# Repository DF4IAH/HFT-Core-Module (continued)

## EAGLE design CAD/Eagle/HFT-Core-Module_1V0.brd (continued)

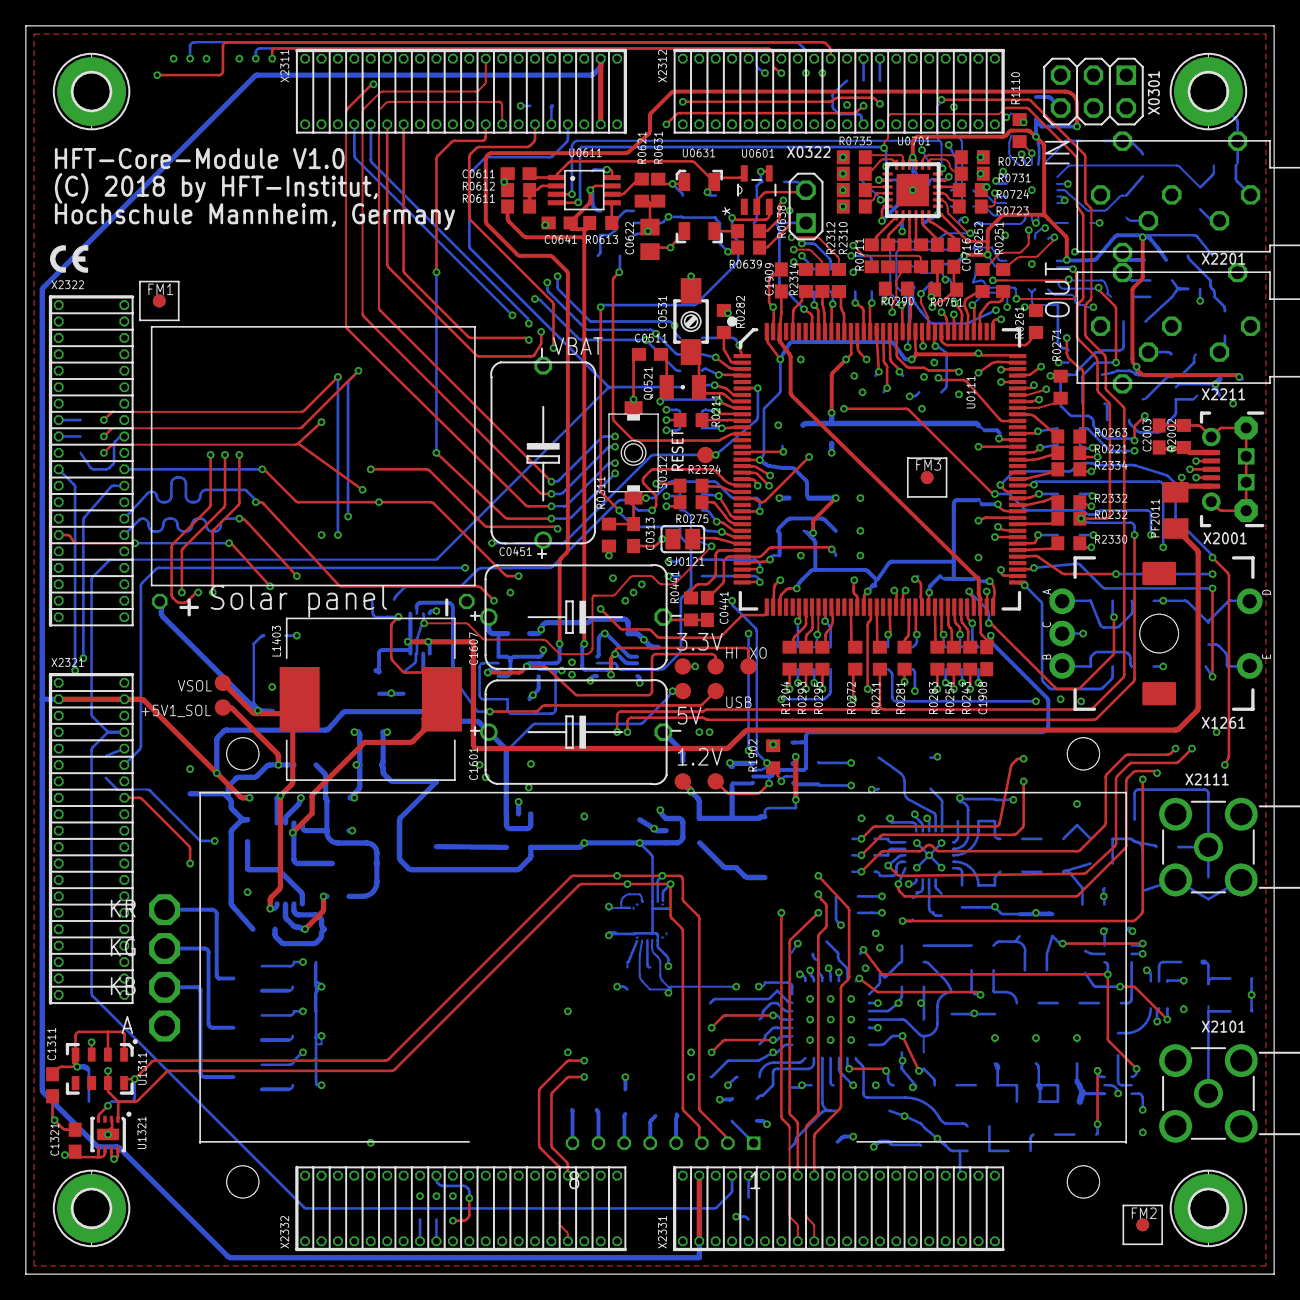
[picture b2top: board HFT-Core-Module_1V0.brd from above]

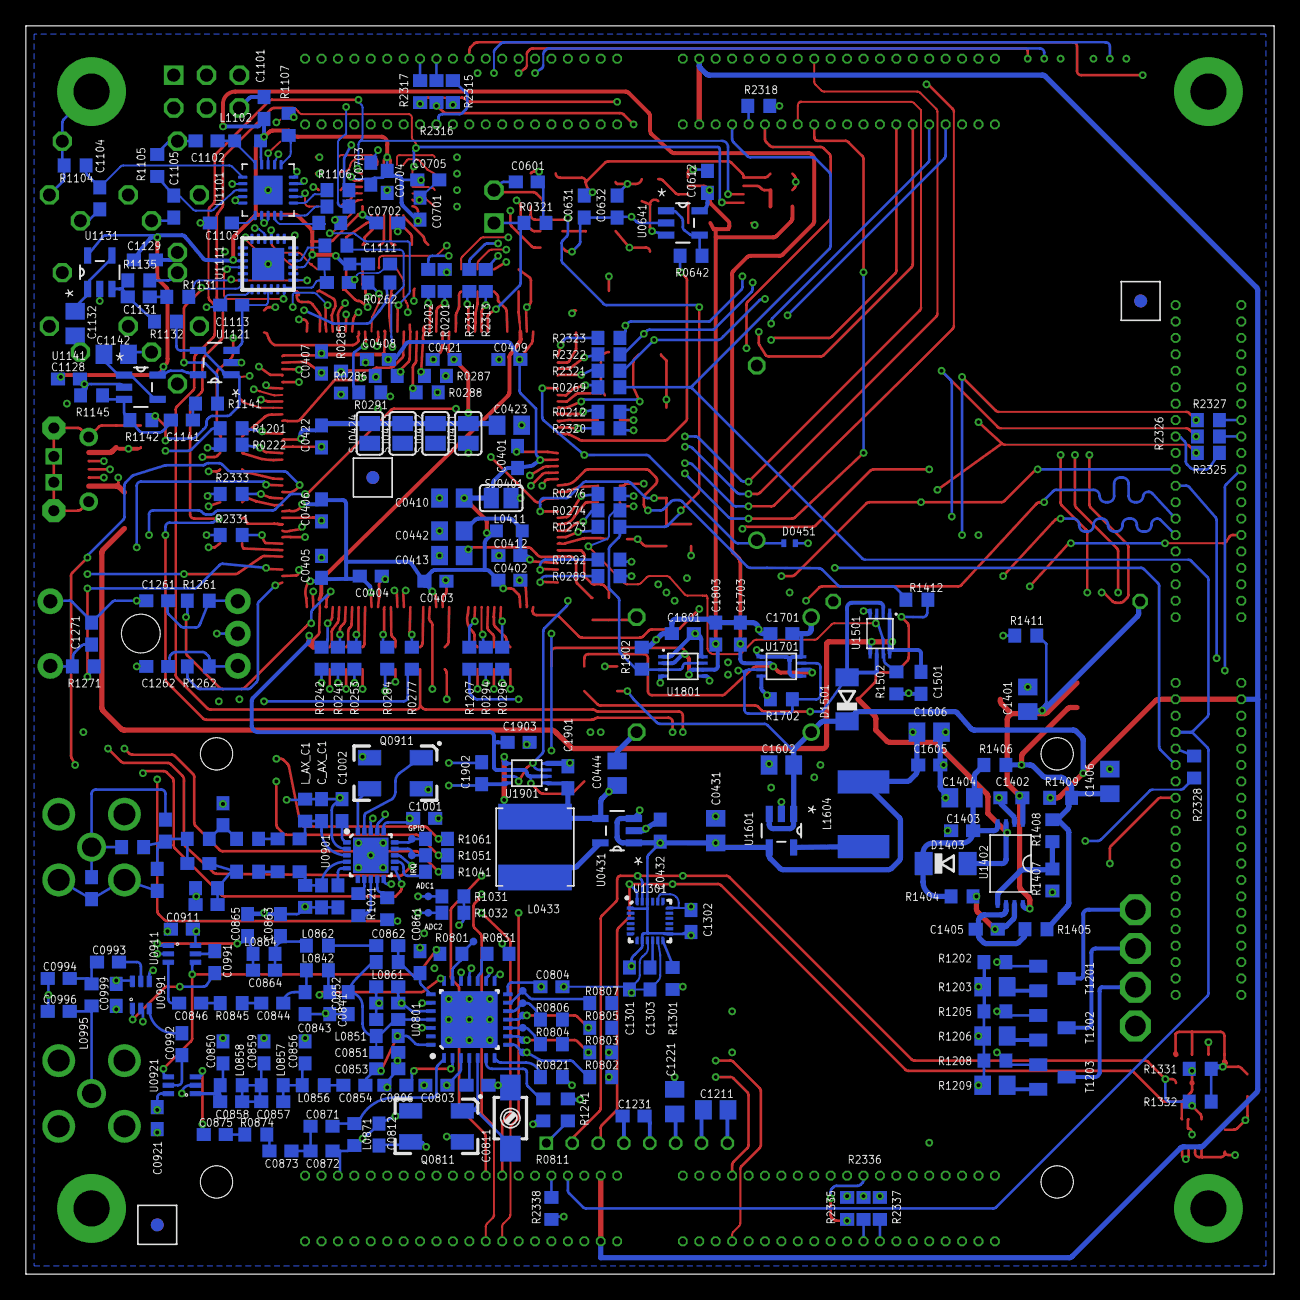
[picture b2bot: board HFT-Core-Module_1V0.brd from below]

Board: 4 copper layers, 96.5 x 96.5 mm, 402 parts (288 on the bottom side), 325 nets.

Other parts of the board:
FM1, FM2, FM3: FIDUCIAL_MARK_1MM

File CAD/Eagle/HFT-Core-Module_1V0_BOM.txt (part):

Stückliste exportiert aus /Users/espero/nfs_ds_nfs/git/HFT-Core-Module__HW_1V0/CAD/Eagle/HFT-Core-Module_1V0.sch am 10.08.18 23:08

Qty Value                                             Device                             Package                            Parts                                                                                                                                                                                                                                                                                                                                                                                                                                                                                                                                                                                                      Description                                                 
1                                                     HEADER-1X2                         1X02                               X0322                                                                                                                                                                                                                                                                                                                                                                                                                                                                                                                                                                                                      Header 1X2 2.54mm                                           
1                                                     HEADER-2X3                         2X03                               X0301                                                                                                                                                                                                                                                                                                                                                                                                                                                                                                                                                                                                      Header 2X3 2.54mm                                           
6                                                     SJ                                 SJ                                 SJ0121, SJ0401, SJ0421, SJ0422, SJ0423, SJ0424                                                                                                                                                                                                                                                                                                                                                                                                                                                                                                                                                             SMD solder JUMPER                                           
18  0R                                                R-EU_R0603                         R0603                              R0201, R0202, R0211, R0212, R0221, R0222, R0231, R0232, R0441, R0612, R0613, R0811, R0845, R0874, R1404, R1405, R1406, R1409                                                                                                                                                                                                                                                                                                                                                                                                                                                                               RESISTOR, European symbol                                   
3   0R                                                R-US_R0603                         R0603                              L0856, L0858, L0995                                                                                                                                                                                                                                                                                                                                                                                                                                                                                                                                                                                        RESISTOR, American symbol                                   
1   0nF                                               C-EUC0603                          C0603                              C1405                                                                                                                                                                                                                                                                                                                                                                                                                                                                                                                                                                                                      CAPACITOR, European symbol                                  
2   0nF HiQ                                           C-EUC0603                          C0603                              C0994, C0996                                                                                                                                                                                                                                                                                                                                                                                                                                                                                                                                                                                               CAPACITOR, European symbol                                  
7   0pF                                               C-EUC0603                          C0603                              C0841, C0850, C0858, C0872, C_AX_C1, C_AX_C2, C_AX_M2                                                                                                                                                                                                                                                                                                                                                                                                                                                                                                                                                      CAPACITOR, European symbol                                  
1   1.0uH 33mR                                        L-EUL5650M                         L5650M                             L1604                                                                                                                                                                                                                                                                                                                                                                                                                                                                                                                                                                                                      INDUCTOR, European symbol                                   
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
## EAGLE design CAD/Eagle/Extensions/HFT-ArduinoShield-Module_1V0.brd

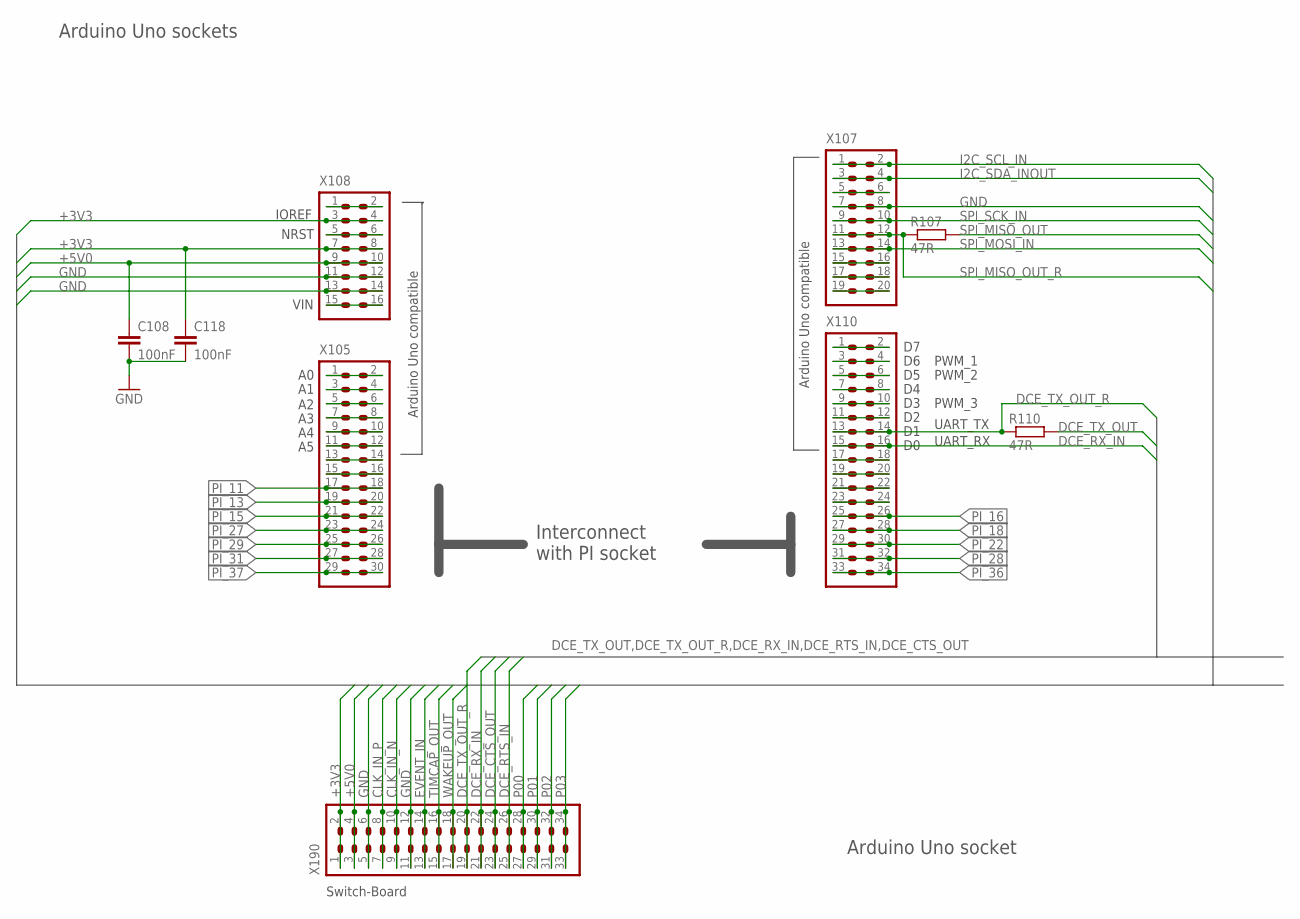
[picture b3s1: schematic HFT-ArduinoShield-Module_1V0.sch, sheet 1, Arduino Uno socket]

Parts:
C108, C118: 100nF; C0603
R107, R110: 47R; R0603
X105: 2X15_2MM56_SOCKET; 2X15
X107: 2X10_2MM56_SOCKET; 2X10
X108: 2X08_2MM56_SOCKET; 2X08
X110, X190: 2X17_2MM56_SOCKET; 2X17

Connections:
+3V3: C118.1, X108.3, X108.4, X108.7, X108.8, X190.1, X190.2; also elsewhere on the board
+5V0: C108.1, X108.9, X108.10, X190.3, X190.4; also elsewhere on the board
CLK_IN_N: X190.9, X190.10; also elsewhere on the board
CLK_IN_P: X190.7, X190.8; also elsewhere on the board
DCE_CTS_OUT: X190.23, X190.24; also elsewhere on the board
DCE_RTS_IN: X190.25, X190.26; also elsewhere on the board
DCE_RX_IN: X110.15, X110.16, X190.21, X190.22; also elsewhere on the board
DCE_TX_OUT: R110.2; also elsewhere on the board
DCE_TX_OUT_R: R110.1, X110.13, X110.14, X190.19, X190.20; also elsewhere on the board
EVENT_IN: X190.13, X190.14; also elsewhere on the board
GND: C108.2, C118.2, X107.7, X107.8, X108.11, X108.12, X108.13, X108.14, X190.5, X190.6, X190.11, X190.12; also elsewhere on the board
I2C_SCL_IN: X107.1, X107.2; also elsewhere on the board
I2C_SDA_INOUT: X107.3, X107.4; also elsewhere on the board
N105_01: X105.1, X105.2
N105_03: X105.3, X105.4
N105_05: X105.5, X105.6
N105_07: X105.7, X105.8
N105_09: X105.9, X105.10
N105_11: X105.11, X105.12
N105_13: X105.13, X105.14
N105_15: X105.15, X105.16
N107_05: X107.5, X107.6
N107_15: X107.15, X107.16
N107_17: X107.17, X107.18
N107_19: X107.19, X107.20
N108_01: X108.1, X108.2
N108_05: X108.5, X108.6
N108_15: X108.15, X108.16
N110_01: X110.1, X110.2
N110_03: X110.3, X110.4
N110_05: X110.5, X110.6
N110_07: X110.7, X110.8
N110_09: X110.9, X110.10
N110_11: X110.11, X110.12
N110_17: X110.17, X110.18
N110_19: X110.19, X110.20
N110_21: X110.21, X110.22
N110_23: X110.23, X110.24
P00: X190.27, X190.28; also elsewhere on the board
P01: X190.29, X190.30; also elsewhere on the board
P02: X190.31, X190.32; also elsewhere on the board
P03: X190.33, X190.34; also elsewhere on the board
PI_11: X105.17, X105.18; also elsewhere on the board
PI_13: X105.19, X105.20; also elsewhere on the board
PI_15: X105.21, X105.22; also elsewhere on the board
PI_16: X110.25, X110.26; also elsewhere on the board
PI_18: X110.27, X110.28; also elsewhere on the board
PI_22: X110.29, X110.30; also elsewhere on the board
PI_27: X105.23, X105.24; also elsewhere on the board
PI_28: X110.31, X110.32; also elsewhere on the board
PI_29: X105.25, X105.26; also elsewhere on the board
PI_31: X105.27, X105.28; also elsewhere on the board
PI_36: X110.33, X110.34; also elsewhere on the board
PI_37: X105.29, X105.30; also elsewhere on the board
SPI_MISO_OUT: R107.2; also elsewhere on the board
SPI_MISO_OUT_R: R107.1, X107.11, X107.12; also elsewhere on the board
SPI_MOSI_IN: X107.13, X107.14; also elsewhere on the board
SPI_SCK_IN: X107.9, X107.10; also elsewhere on the board
TIMCAP_OUT: X190.15, X190.16; also elsewhere on the board
WAKEUP_OUT: X190.17, X190.18; also elsewhere on the board

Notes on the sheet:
NRST
Arduino Uno compatible
Switch-Board
Arduino Uno socket
IOREF
VIN
UART_RX
UART_TX
PWM_1
PWM_2
PWM_3
Arduino Uno sockets
Interconnect with PI socket

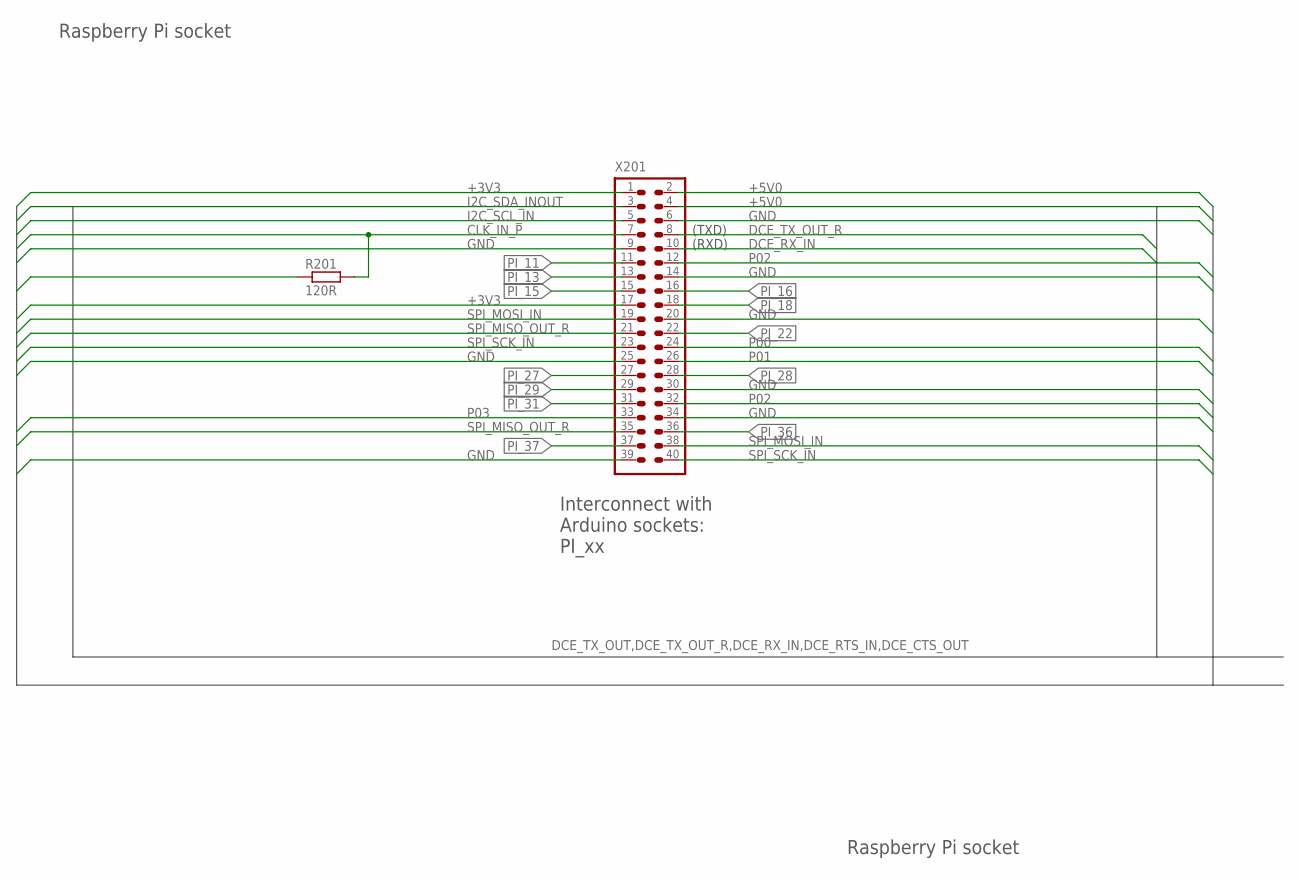
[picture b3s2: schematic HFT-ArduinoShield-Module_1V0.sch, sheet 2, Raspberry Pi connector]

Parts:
R201: 120R; R0603
X201: 2X20_2MM56_SOCKET; 2X20

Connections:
+3V3: X201.1, X201.17; also elsewhere on the board
+5V0: X201.2, X201.4; also elsewhere on the board
CLK_IN_N: R201.1; also elsewhere on the board
CLK_IN_P: R201.2, X201.7; also elsewhere on the board
DCE_RX_IN: X201.10; also elsewhere on the board
DCE_TX_OUT_R: X201.8; also elsewhere on the board
GND: X201.6, X201.9, X201.14, X201.20, X201.25, X201.30, X201.34, X201.39; also elsewhere on the board
I2C_SCL_IN: X201.5; also elsewhere on the board
I2C_SDA_INOUT: X201.3; also elsewhere on the board
P00: X201.24; also elsewhere on the board
P01: X201.26; also elsewhere on the board
P02: X201.12, X201.32; also elsewhere on the board
P03: X201.33; also elsewhere on the board
PI_11: X201.11; also elsewhere on the board
PI_13: X201.13; also elsewhere on the board
PI_15: X201.15; also elsewhere on the board
PI_16: X201.16; also elsewhere on the board
PI_18: X201.18; also elsewhere on the board
PI_22: X201.22; also elsewhere on the board
PI_27: X201.27; also elsewhere on the board
PI_28: X201.28; also elsewhere on the board
PI_29: X201.29; also elsewhere on the board
PI_31: X201.31; also elsewhere on the board
PI_36: X201.36; also elsewhere on the board
PI_37: X201.37; also elsewhere on the board
SPI_MISO_OUT_R: X201.21, X201.35; also elsewhere on the board
SPI_MOSI_IN: X201.19, X201.38; also elsewhere on the board
SPI_SCK_IN: X201.23, X201.40; also elsewhere on the board

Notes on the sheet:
Raspberry Pi socket
(TXD)
(RXD)
Interconnect with Arduino sockets: PI_xx

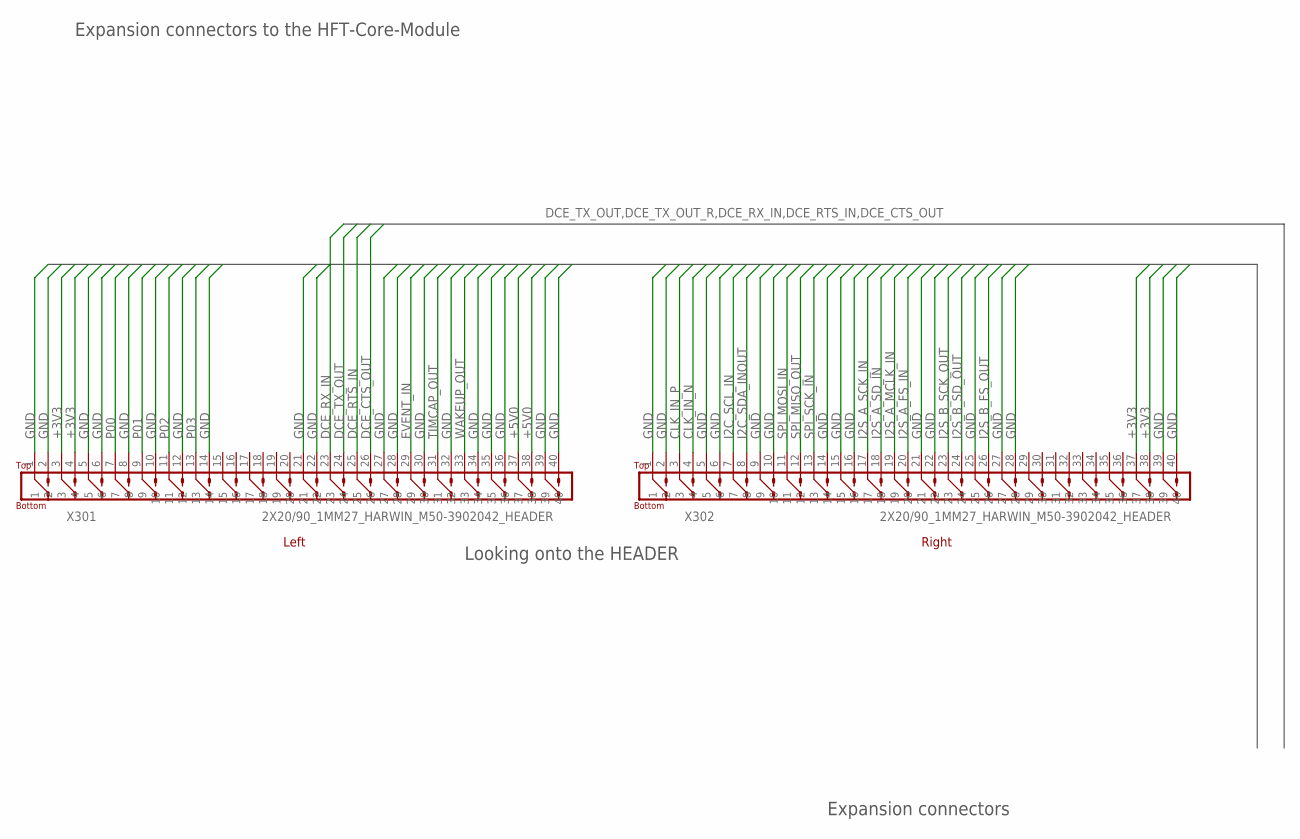
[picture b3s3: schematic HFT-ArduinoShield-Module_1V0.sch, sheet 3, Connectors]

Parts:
X301, X302: 2X20/90_1MM27_HARWIN_M50-3902042_HEADER

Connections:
+3V3: X301.3, X301.4, X302.37, X302.38; also elsewhere on the board
+5V0: X301.37, X301.38; also elsewhere on the board
CLK_IN_N: X302.4; also elsewhere on the board
CLK_IN_P: X302.3; also elsewhere on the board
DCE_CTS_OUT: X301.26; also elsewhere on the board
DCE_RTS_IN: X301.25; also elsewhere on the board
DCE_RX_IN: X301.23; also elsewhere on the board
DCE_TX_OUT: X301.24; also elsewhere on the board
EVENT_IN: X301.29; also elsewhere on the board
GND: X301.1, X301.2, X301.5, X301.6, X301.8, X301.10, X301.12, X301.14, X301.21, X301.22, X301.27, X301.28, X301.30, X301.32, X301.34, X301.35, X301.36, X301.39, X301.40, X302.1, X302.2, X302.5, X302.6, X302.9, X302.10, X302.14, X302.15, X302.16, X302.21, X302.22, X302.25, X302.27, X302.28, X302.39, X302.40; also elsewhere on the board
I2C_SCL_IN: X302.7; also elsewhere on the board
I2C_SDA_INOUT: X302.8; also elsewhere on the board
I2S_A_FS_IN: X302.20
I2S_A_MCLK_IN: X302.19
I2S_A_SCK_IN: X302.17
I2S_A_SD_IN: X302.18
I2S_B_FS_OUT: X302.26
I2S_B_SCK_OUT: X302.23
I2S_B_SD_OUT: X302.24
P00: X301.7; also elsewhere on the board
P01: X301.9; also elsewhere on the board
P02: X301.11; also elsewhere on the board
P03: X301.13; also elsewhere on the board
SPI_MISO_OUT: X302.12; also elsewhere on the board
SPI_MOSI_IN: X302.11; also elsewhere on the board
SPI_SCK_IN: X302.13; also elsewhere on the board
TIMCAP_OUT: X301.31; also elsewhere on the board
WAKEUP_OUT: X301.33; also elsewhere on the board

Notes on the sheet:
Left
Right
Expansion connectors
Looking onto the HEADER
Expansion connectors to the HFT-Core-Module

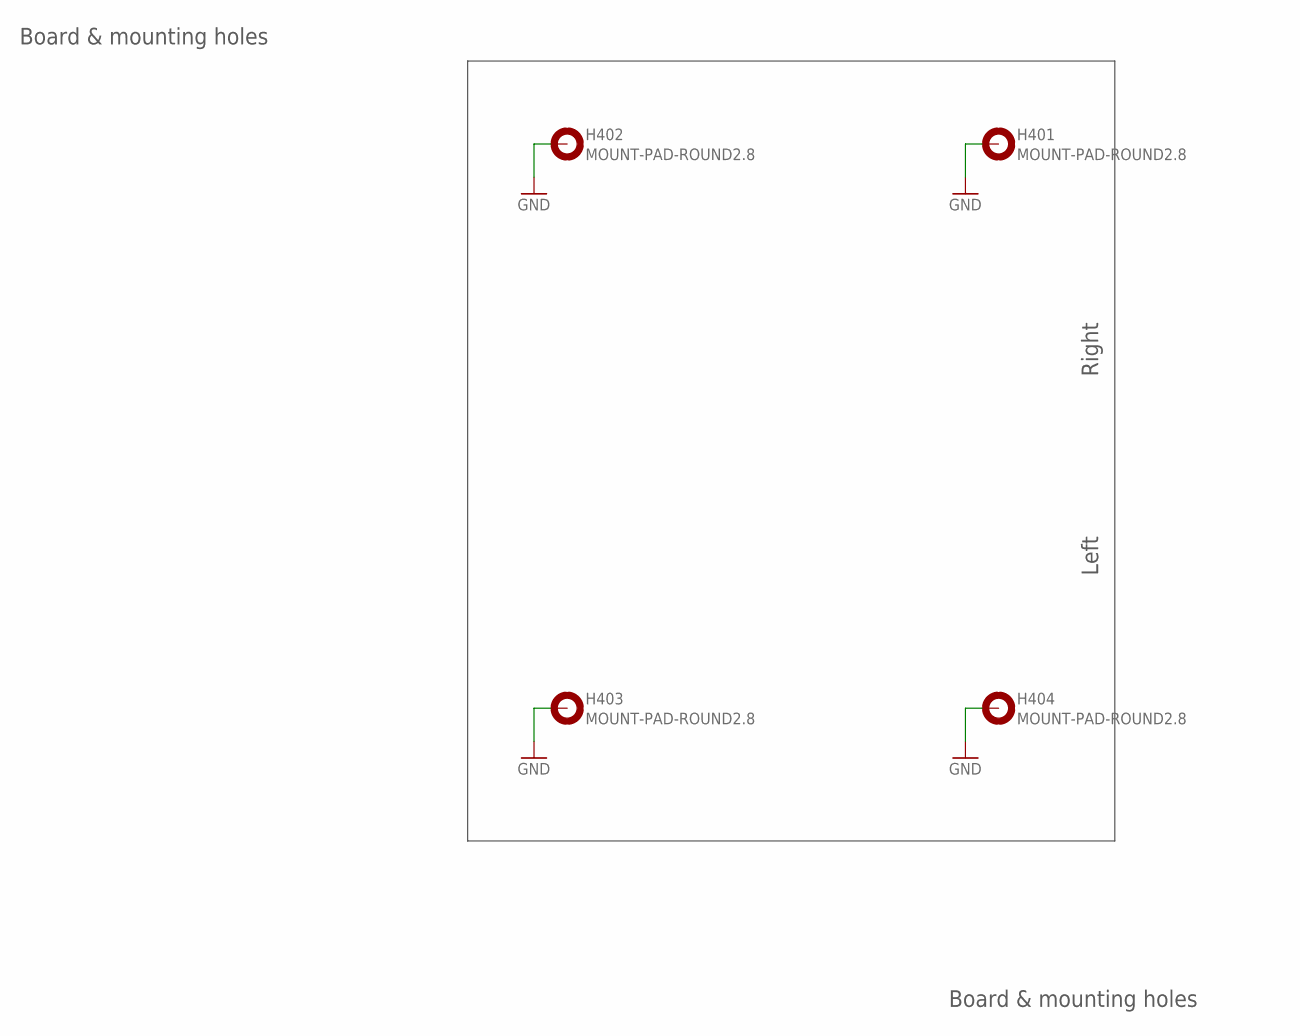
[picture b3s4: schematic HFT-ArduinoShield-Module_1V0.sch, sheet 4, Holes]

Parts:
H401, H402, H403, H404: MOUNT-PAD-ROUND2.8; 2,8-PAD

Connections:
GND: H401.B2,8, H402.B2,8, H403.B2,8, H404.B2,8; also elsewhere on the board

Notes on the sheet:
Board & mounting holes
Left
Right

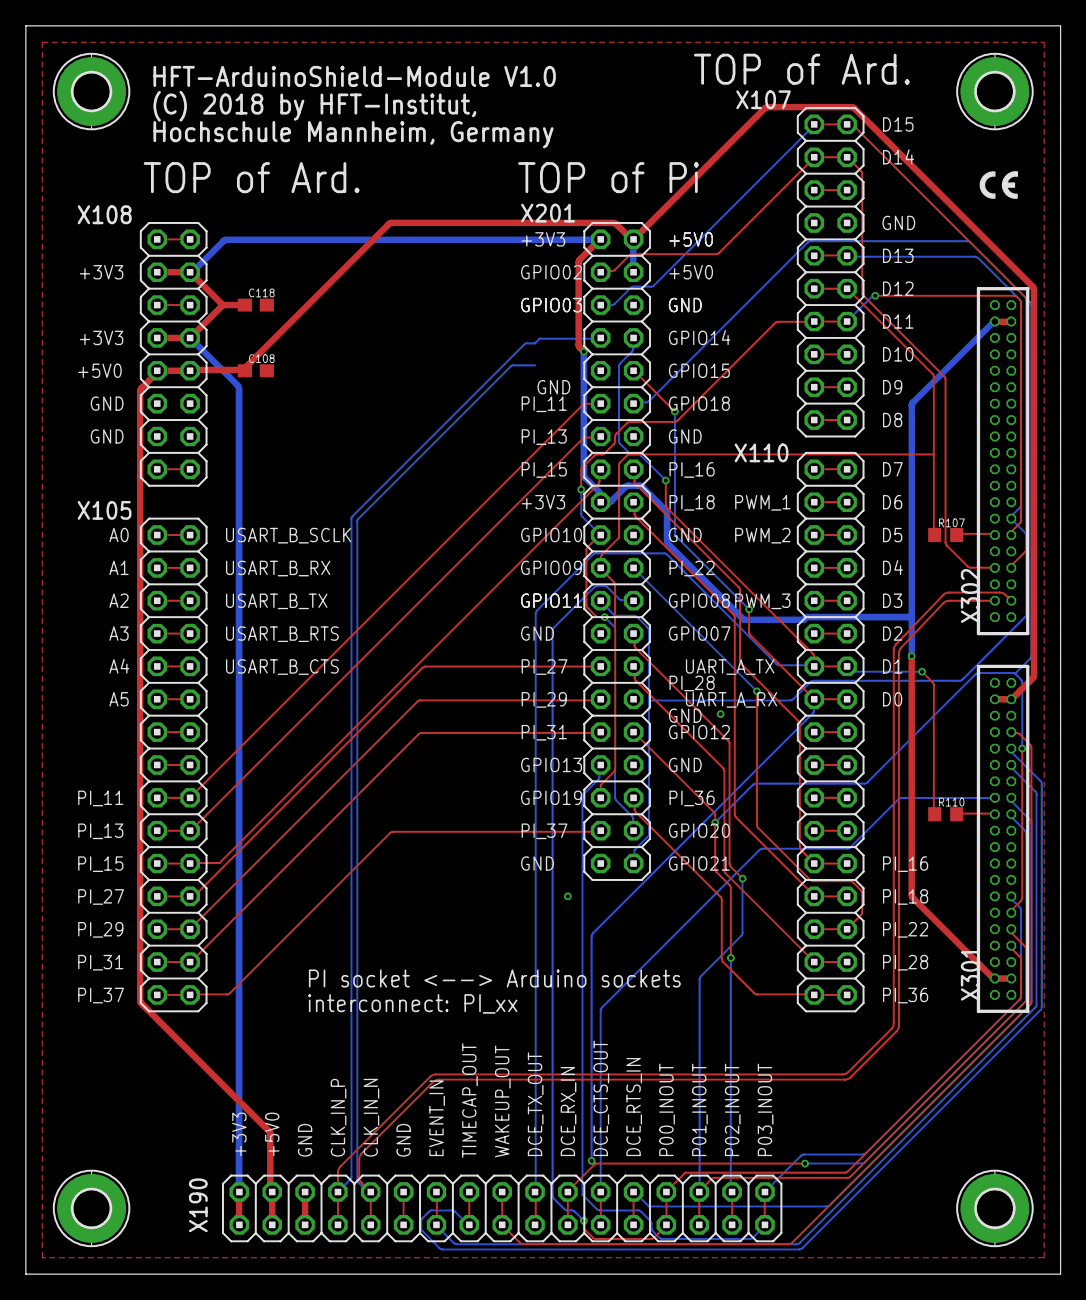
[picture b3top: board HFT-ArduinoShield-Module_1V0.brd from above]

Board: 4 copper layers, 80.0 x 96.5 mm, 17 parts (1 on the bottom side), 60 nets.

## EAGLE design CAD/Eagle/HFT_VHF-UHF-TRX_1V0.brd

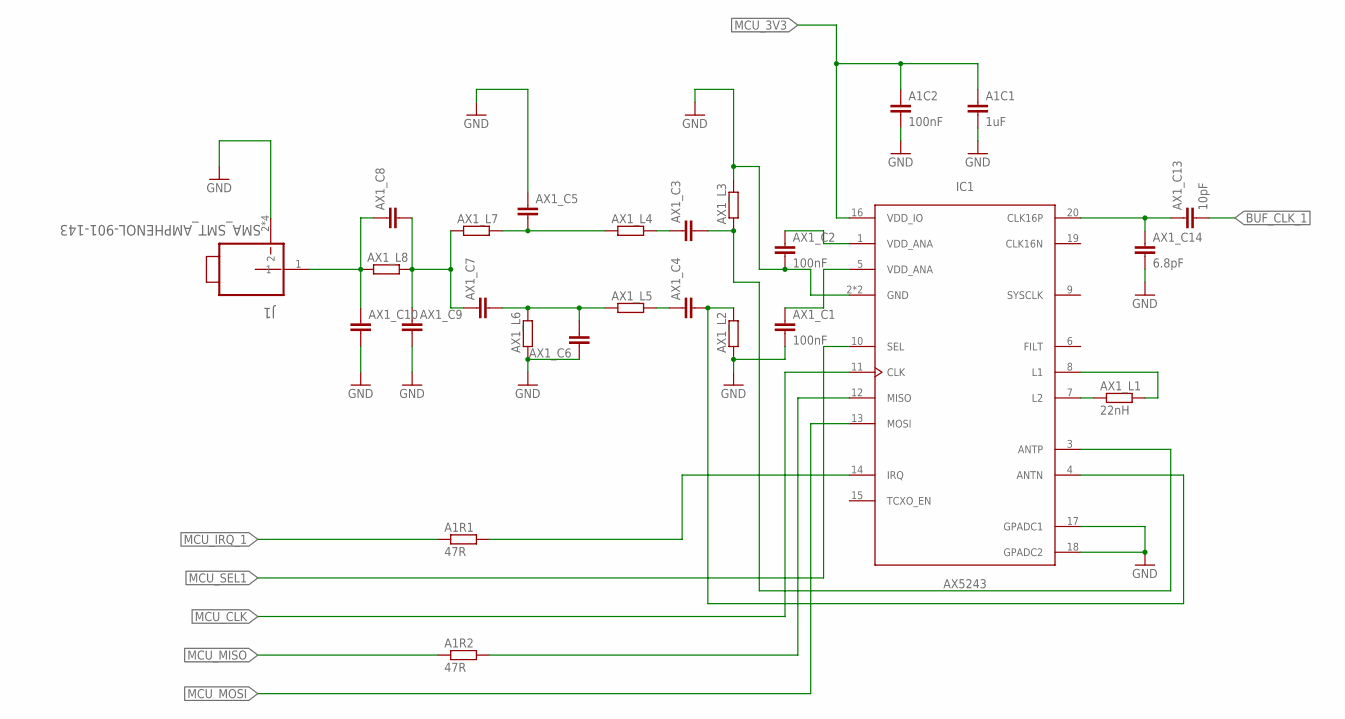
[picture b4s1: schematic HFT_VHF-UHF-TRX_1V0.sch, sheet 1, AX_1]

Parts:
A1C1: 1uF; C0805
A1C2: 100nF; C0805
A1R1, A1R2: 47R; R0805
AX1_C1, AX1_C2: 100nF; C0805
AX1_C3, AX1_C4, AX1_C5, AX1_C6, AX1_C7, AX1_C8, AX1_C9, AX1_C10: C-EUC0805; C0805
AX1_C13: 10pF; C0805
AX1_C14: 6.8pF; C0805
AX1_L1: 22nH; R0805
AX1_L2, AX1_L3, AX1_L4, AX1_L5, AX1_L6, AX1_L7, AX1_L8: R-EU_R0805; R0805
IC1: AX5243; QFN20-4X4-0P5-PAD
J1: SMA_SMT_AMPHENOL-901-143; SMA_SMT_AMPHENOL_901-143

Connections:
AX1_C3_L4: AX1_C3.1, AX1_L4.2
AX1_C4_L5: AX1_C4.1, AX1_L5.2
AX1_CH1_ANA1: AX1_C2.1, IC1.1 (VDD_ANA)
AX1_CH1_ANA2: AX1_C1.1, IC1.5 (VDD_ANA)
AX1_CH1_ANTN: AX1_C4.2, AX1_L2.2, IC1.4 (ANTN)
AX1_CH1_ANTP: AX1_C3.2, AX1_L3.1, IC1.3 (ANTP)
AX1_CH_1: AX1_C8.1, AX1_C10.1, AX1_L8.1, J1.1
AX1_IRQ_1: A1R1.2, IC1.14 (IRQ)
AX1_L1: AX1_L1.2, IC1.8 (L1)
AX1_L2: AX1_L1.1, IC1.7 (L2)
AX1_L4_C5_L7: AX1_C5.2, AX1_L4.1, AX1_L7.2
AX1_L4_C7_L8: AX1_C7.1, AX1_C8.2, AX1_C9.1, AX1_L7.1, AX1_L8.2
AX1_L5_C6_L6_C7: AX1_C6.2, AX1_C7.2, AX1_L5.1, AX1_L6.2
AX1_MISO: A1R2.2, IC1.12 (MISO)
BUF_CLK_1: AX1_C13.2; also elsewhere on the board
BUF_CLK_A1: AX1_C13.1, AX1_C14.1, IC1.20 (CLK16P)
GND: A1C1.2, A1C2.2, AX1_C1.2, AX1_C2.2, AX1_C5.1, AX1_C6.1, AX1_C9.2, AX1_C10.2, AX1_C14.2, AX1_L2.1, AX1_L3.2, AX1_L6.1, IC1.2 (GND), IC1.17 (GPADC1), IC1.18 (GPADC2), IC1.21 (GND), J1.2, J1.3 (2), J1.4 (2), J1.5 (2); also elsewhere on the board
MCU_3V3: A1C1.1, A1C2.1, IC1.16 (VDD_IO); also elsewhere on the board
MCU_CLK: IC1.11 (CLK); also elsewhere on the board
MCU_IRQ_1: A1R1.1; also elsewhere on the board
MCU_MISO: A1R2.1; also elsewhere on the board
MCU_MOSI: IC1.13 (MOSI); also elsewhere on the board
MCU_SEL1: IC1.10 (SEL); also elsewhere on the board

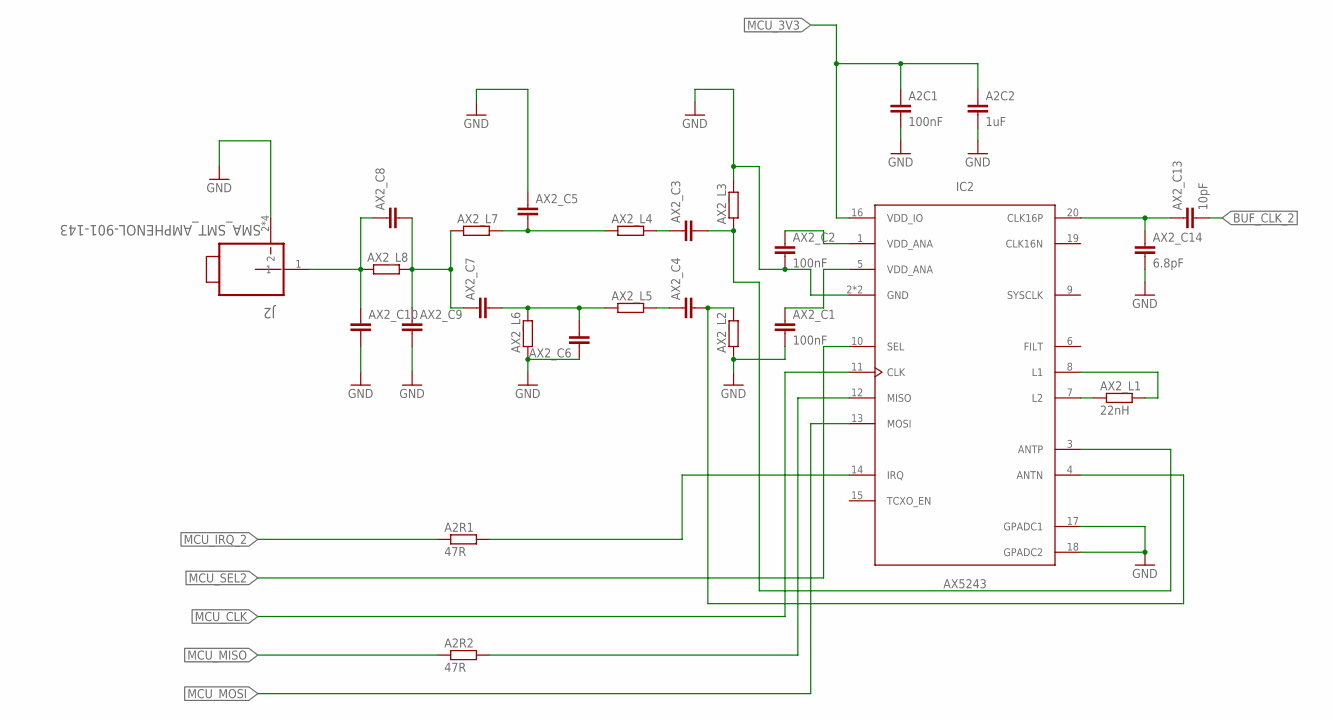
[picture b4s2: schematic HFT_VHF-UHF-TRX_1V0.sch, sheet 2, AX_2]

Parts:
A2C1: 100nF; C0805
A2C2: 1uF; C0805
A2R1, A2R2: 47R; R0805
AX2_C1, AX2_C2: 100nF; C0805
AX2_C3, AX2_C4, AX2_C5, AX2_C6, AX2_C7, AX2_C8, AX2_C9, AX2_C10: C-EUC0805; C0805
AX2_C13: 10pF; C0805
AX2_C14: 6.8pF; C0805
AX2_L1: 22nH; R0805
AX2_L2, AX2_L3, AX2_L4, AX2_L5, AX2_L6, AX2_L7, AX2_L8: R-EU_R0805; R0805
IC2: AX5243; QFN20-4X4-0P5-PAD
J2: SMA_SMT_AMPHENOL-901-143; SMA_SMT_AMPHENOL_901-143

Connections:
AX2_C3_L4: AX2_C3.1, AX2_L4.2
AX2_C4_L5: AX2_C4.1, AX2_L5.2
AX2_CH2_ANA1: AX2_C2.1, IC2.1 (VDD_ANA)
AX2_CH2_ANA2: AX2_C1.1, IC2.5 (VDD_ANA)
AX2_CH2_ANTN: AX2_C4.2, AX2_L2.2, IC2.4 (ANTN)
AX2_CH2_ANTP: AX2_C3.2, AX2_L3.1, IC2.3 (ANTP)
AX2_CH_2: AX2_C8.1, AX2_C10.1, AX2_L8.1, J2.1
AX2_IRQ_2: A2R1.2, IC2.14 (IRQ)
AX2_L1: AX2_L1.2, IC2.8 (L1)
AX2_L2: AX2_L1.1, IC2.7 (L2)
AX2_L4_C5_L7: AX2_C5.2, AX2_L4.1, AX2_L7.2
AX2_L4_C7_L8: AX2_C7.1, AX2_C8.2, AX2_C9.1, AX2_L7.1, AX2_L8.2
AX2_L5_C6_L6_C7: AX2_C6.2, AX2_C7.2, AX2_L5.1, AX2_L6.2
AX2_MISO: A2R2.2, IC2.12 (MISO)
BUF_CLK_2: AX2_C13.2; also elsewhere on the board
BUF_CLK_A2: AX2_C13.1, AX2_C14.1, IC2.20 (CLK16P)
GND: A2C1.2, A2C2.2, AX2_C1.2, AX2_C2.2, AX2_C5.1, AX2_C6.1, AX2_C9.2, AX2_C10.2, AX2_C14.2, AX2_L2.1, AX2_L3.2, AX2_L6.1, IC2.2 (GND), IC2.17 (GPADC1), IC2.18 (GPADC2), IC2.21 (GND), J2.2, J2.3 (2), J2.4 (2), J2.5 (2); also elsewhere on the board
MCU_3V3: A2C1.1, A2C2.1, IC2.16 (VDD_IO); also elsewhere on the board
MCU_CLK: IC2.11 (CLK); also elsewhere on the board
MCU_IRQ_2: A2R1.1; also elsewhere on the board
MCU_MISO: A2R2.1; also elsewhere on the board
MCU_MOSI: IC2.13 (MOSI); also elsewhere on the board
MCU_SEL2: IC2.10 (SEL); also elsewhere on the board
